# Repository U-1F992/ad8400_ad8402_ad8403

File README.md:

# AD8400/AD8402/AD8403

- https://www.analog.com/products/ad8400.html
- https://www.analog.com/products/ad8402.html
- https://www.analog.com/products/ad8403.html

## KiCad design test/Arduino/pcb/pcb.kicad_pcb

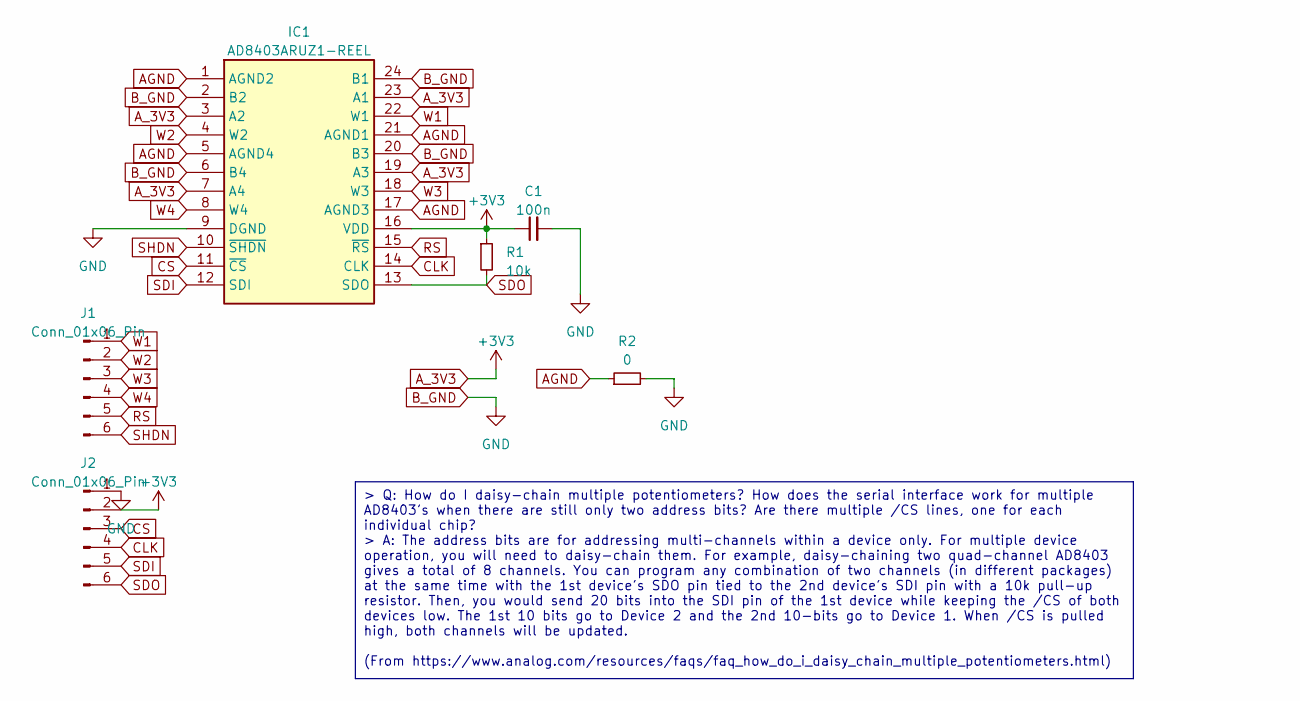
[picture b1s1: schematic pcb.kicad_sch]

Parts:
C1: 100n; C_0603_1608Metric
IC1: AD8403ARUZ1-REEL; SOP65P640X120-24N; Manufacturer_Part_Number AD8403ARUZ1-REEL; Mouser Part Number 584-AD8403ARUZ1-R
J1, J2: Conn_01x06_Pin; PinHeader_1x06_P2.54mm_Vertical
R1: 10k; R_0603_1608Metric
R2: 0; R_0603_1608Metric

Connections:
AGND: IC1.1 (AGND2), IC1.5 (AGND4), IC1.17 (AGND3), IC1.21 (AGND1), R2.1
A_3V3: C1.1, IC1.3 (A2), IC1.7 (A4), IC1.16 (VDD), IC1.19 (A3), IC1.23 (A1), J2.2, R1.1
B_GND: C1.2, IC1.2 (B2), IC1.6 (B4), IC1.9 (DGND), IC1.20 (B3), IC1.24 (B1), J2.1, R2.2
CLK: IC1.14 (CLK), J2.4
CS: IC1.11 (~CS), J2.3
RS: IC1.15 (~RS), J1.5
SDI: IC1.12 (SDI), J2.5
SDO: IC1.13 (SDO), J2.6, R1.2
SHDN: IC1.10 (~SHDN), J1.6
W1: IC1.22 (W1), J1.1
W2: IC1.4 (W2), J1.2
W3: IC1.18 (W3), J1.3
W4: IC1.8 (W4), J1.4

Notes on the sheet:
> Q: How do I daisy-chain multiple potentiometers? How does the serial interface work for multiple AD8403's when there are still only two address bits? Are there multiple /CS lines, one for each individual chip? > A: The address bits are for addressing multi-channels within a device only. For multi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

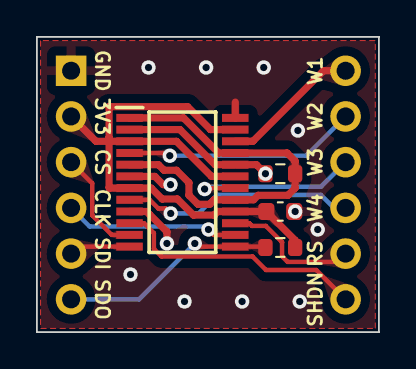
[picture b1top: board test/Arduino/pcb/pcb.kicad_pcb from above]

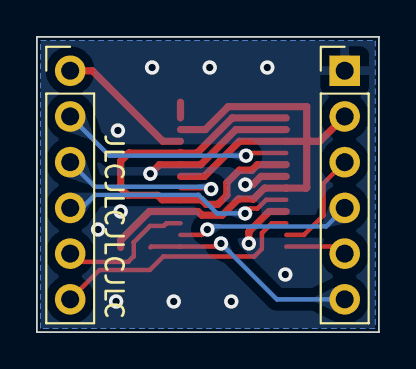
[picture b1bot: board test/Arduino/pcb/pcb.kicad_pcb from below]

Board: 2 copper layers, 19.0 x 16.4 mm, 6 parts (2 on the bottom side), 13 nets.

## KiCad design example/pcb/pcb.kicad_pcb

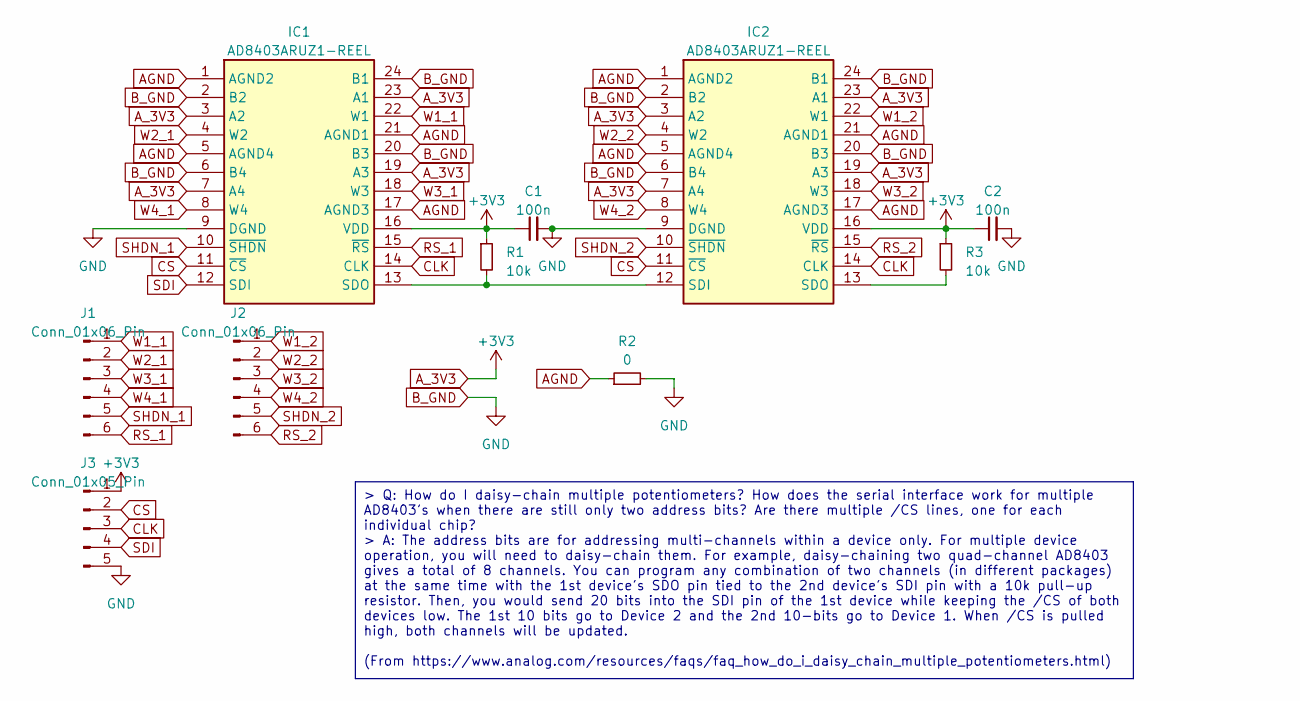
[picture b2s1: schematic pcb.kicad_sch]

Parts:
C1, C2: 100n; C_0603_1608Metric
IC1, IC2: AD8403ARUZ1-REEL; SOP65P640X120-24N; Manufacturer_Part_Number AD8403ARUZ1-REEL; Mouser Part Number 584-AD8403ARUZ1-R
J1, J2: Conn_01x06_Pin; PinHeader_1x06_P2.54mm_Vertical
J3: Conn_01x05_Pin; PinHeader_1x05_P2.54mm_Vertical
R1, R3: 10k; R_0603_1608Metric
R2: 0; R_0603_1608Metric

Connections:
AGND: IC1.1 (AGND2), IC1.5 (AGND4), IC1.17 (AGND3), IC1.21 (AGND1), IC2.1 (AGND2), IC2.5 (AGND4), IC2.17 (AGND3), IC2.21 (AGND1), R2.1
A_3V3: C1.1, C2.1, IC1.3 (A2), IC1.7 (A4), IC1.16 (VDD), IC1.19 (A3), IC1.23 (A1), IC2.3 (A2), IC2.7 (A4), IC2.16 (VDD), IC2.19 (A3), IC2.23 (A1), J3.1, R1.1, R3.1
B_GND: C1.2, C2.2, IC1.2 (B2), IC1.6 (B4), IC1.9 (DGND), IC1.20 (B3), IC1.24 (B1), IC2.2 (B2), IC2.6 (B4), IC2.9 (DGND), IC2.20 (B3), IC2.24 (B1), J3.5, R2.2
CLK: IC1.14 (CLK), IC2.14 (CLK), J3.3
CS: IC1.11 (~CS), IC2.11 (~CS), J3.2
unnamed: IC1.13 (SDO), IC2.12 (SDI), R1.2
unnamed: IC2.13 (SDO), R3.2
RS_1: IC1.15 (~RS), J1.6
RS_2: IC2.15 (~RS), J2.6
SDI: IC1.12 (SDI), J3.4
SHDN_1: IC1.10 (~SHDN), J1.5
SHDN_2: IC2.10 (~SHDN), J2.5
W1_1: IC1.22 (W1), J1.1
W1_2: IC2.22 (W1), J2.1
W2_1: IC1.4 (W2), J1.2
W2_2: IC2.4 (W2), J2.2
W3_1: IC1.18 (W3), J1.3
W3_2: IC2.18 (W3), J2.3
W4_1: IC1.8 (W4), J1.4
W4_2: IC2.8 (W4), J2.4

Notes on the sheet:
> Q: How do I daisy-chain multiple potentiometers? How does the serial interface work for multiple AD8403's when there are still only two address bits? Are there multiple /CS lines, one for each individual chip? > A: The address bits are for addressing multi-channels within a device only. For multi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

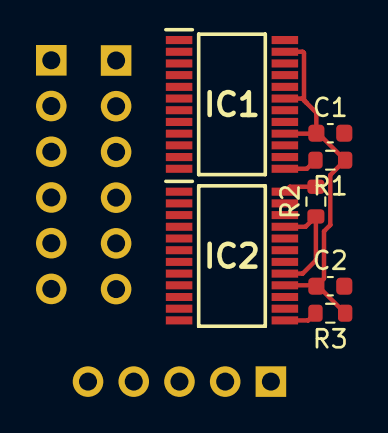
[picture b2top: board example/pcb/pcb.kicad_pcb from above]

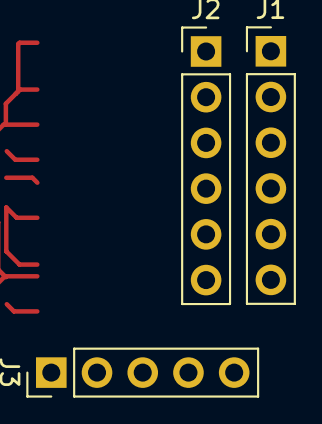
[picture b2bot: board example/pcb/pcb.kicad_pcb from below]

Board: 2 copper layers, 10 parts (3 on the bottom side), 20 nets.

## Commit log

2024-02-20 Refactor function signatures for improved error handling
2024-02-20 Rename identifiers to comply with C standards
2024-02-20 Add tests
2024-02-20 Add example project
2024-02-20 Add wrapper for Arduino
2024-02-21 Add pcb
2024-02-21 Update pcb
2024-03-23 Use errno_t
